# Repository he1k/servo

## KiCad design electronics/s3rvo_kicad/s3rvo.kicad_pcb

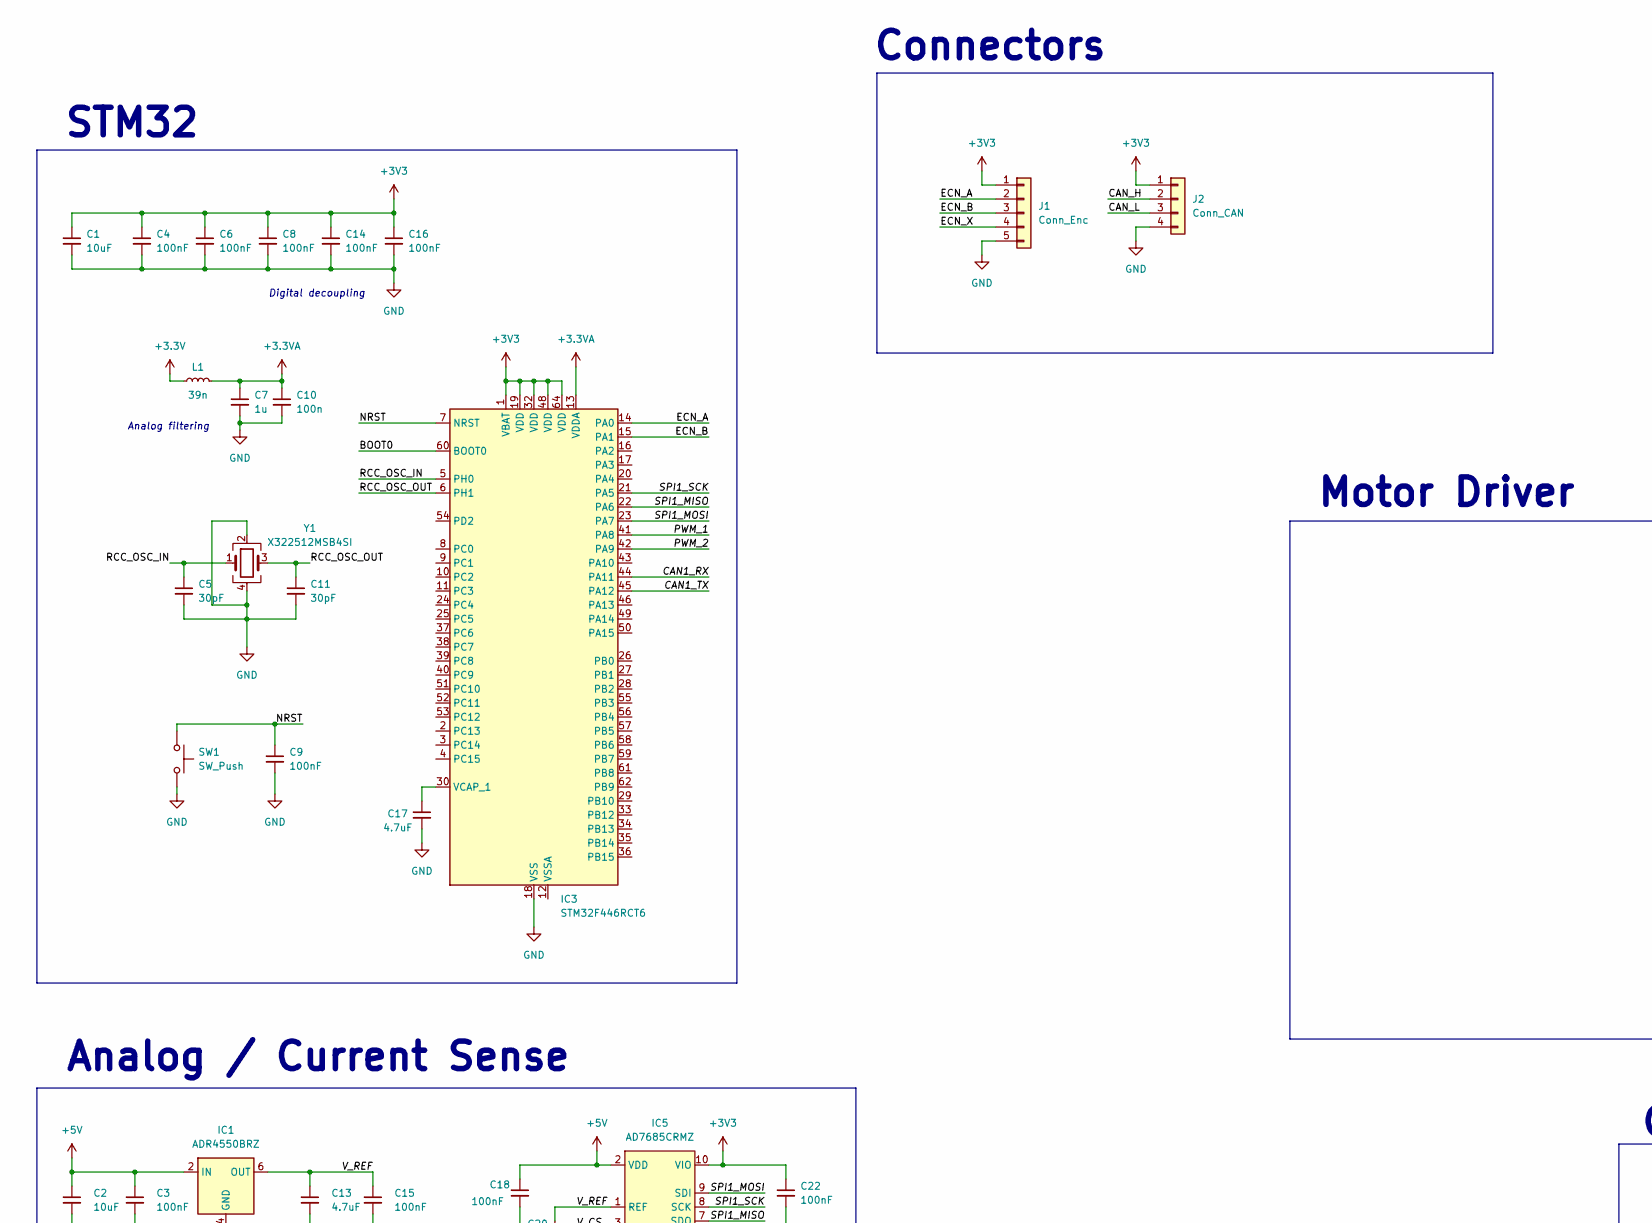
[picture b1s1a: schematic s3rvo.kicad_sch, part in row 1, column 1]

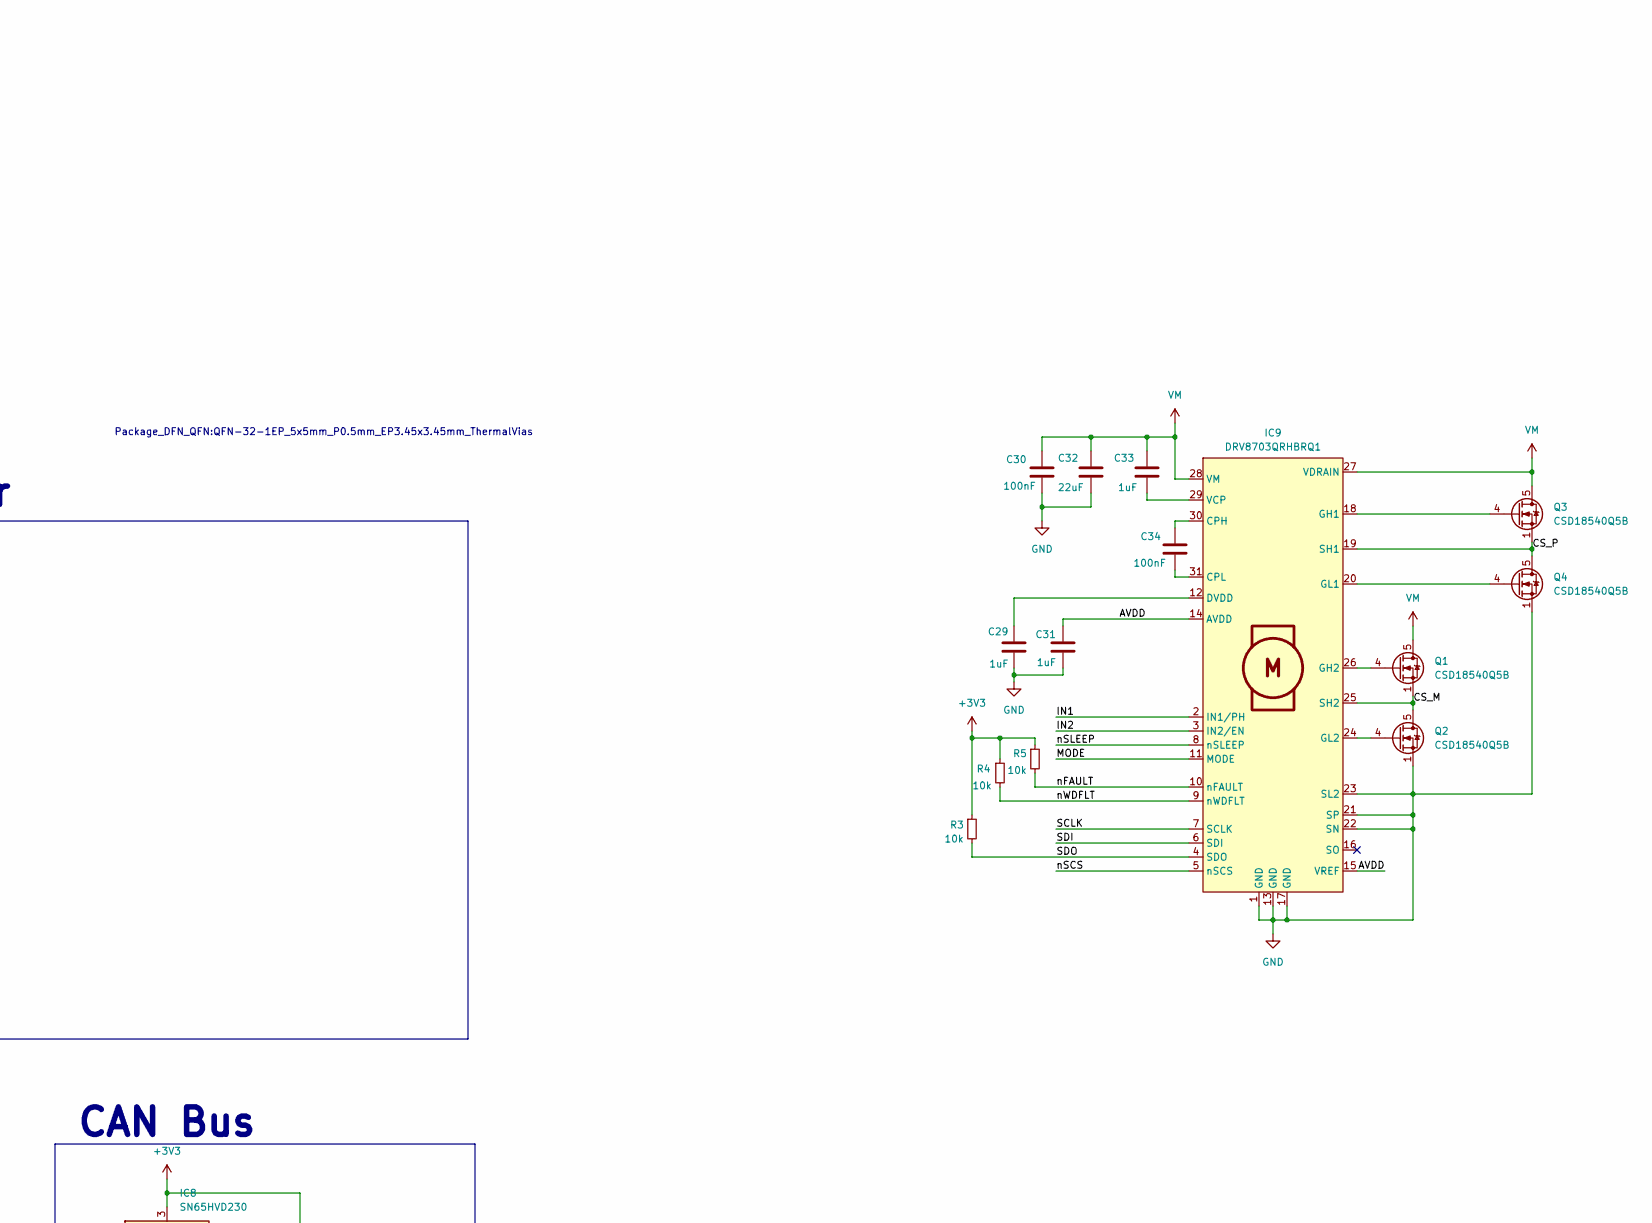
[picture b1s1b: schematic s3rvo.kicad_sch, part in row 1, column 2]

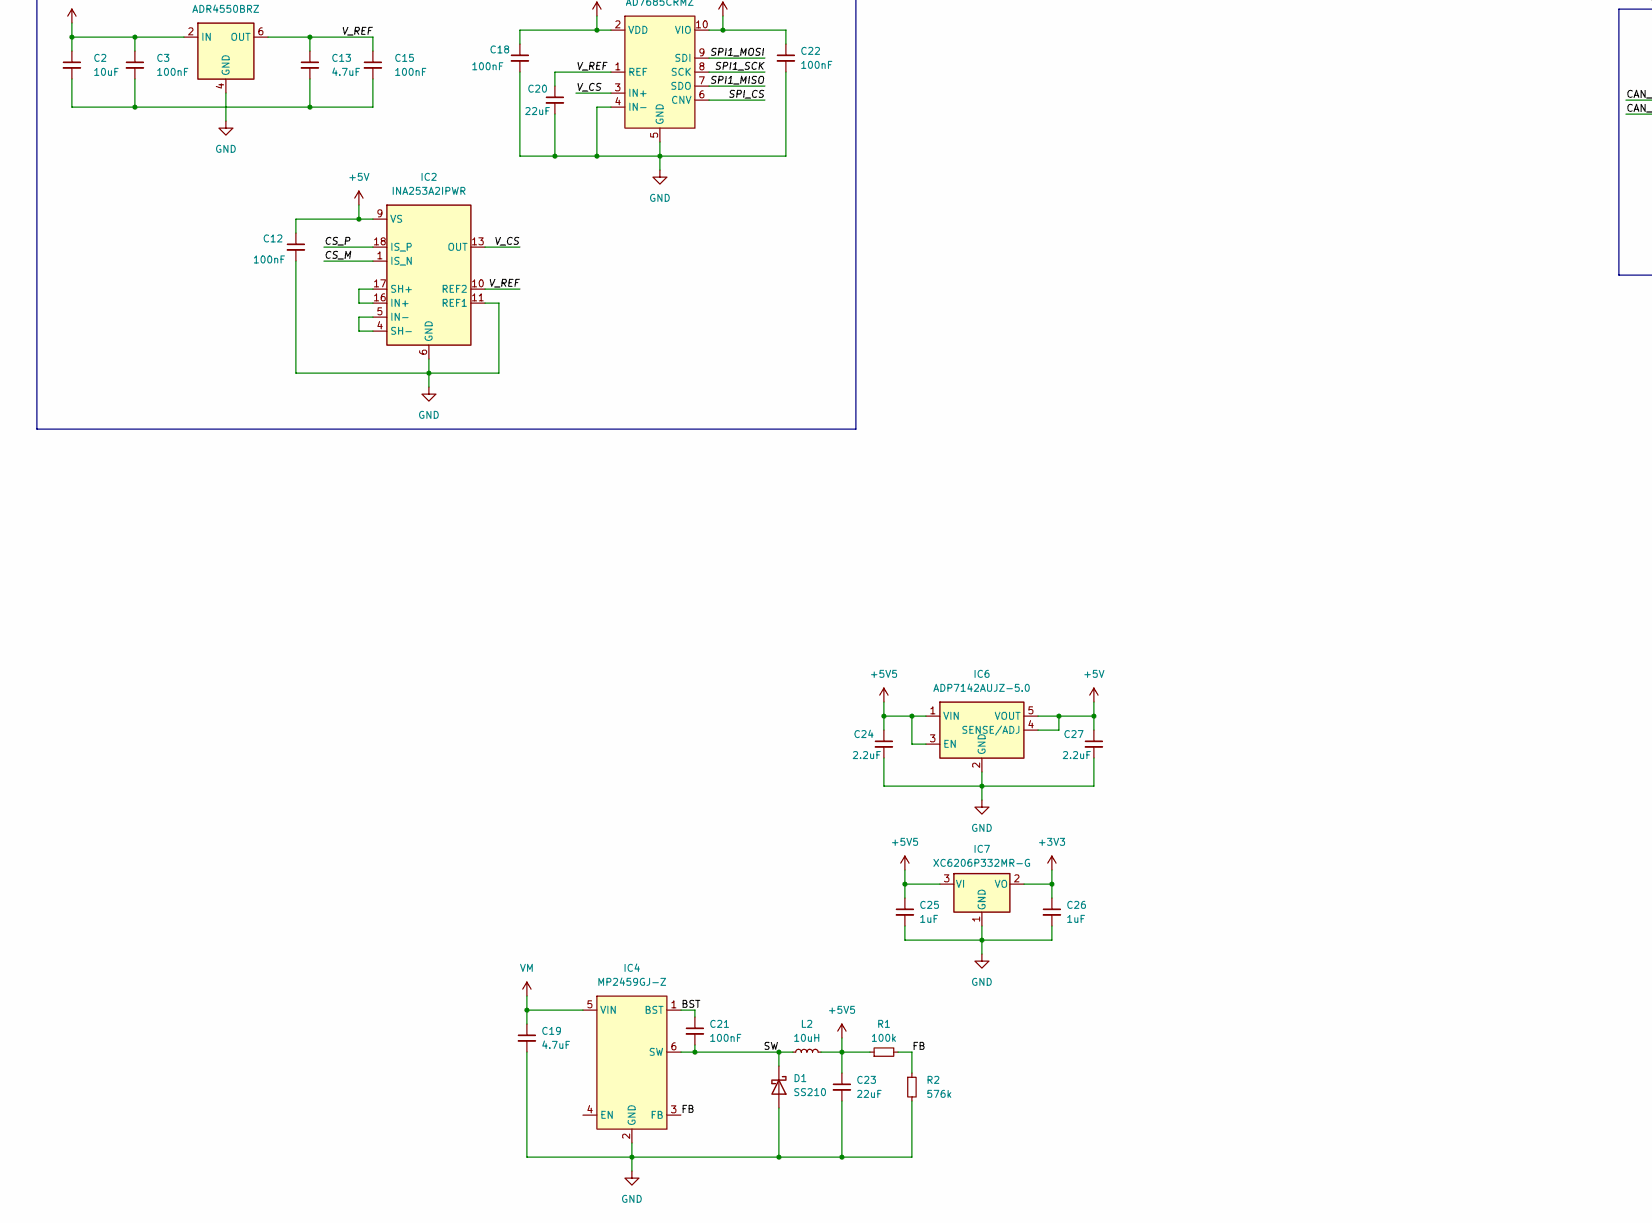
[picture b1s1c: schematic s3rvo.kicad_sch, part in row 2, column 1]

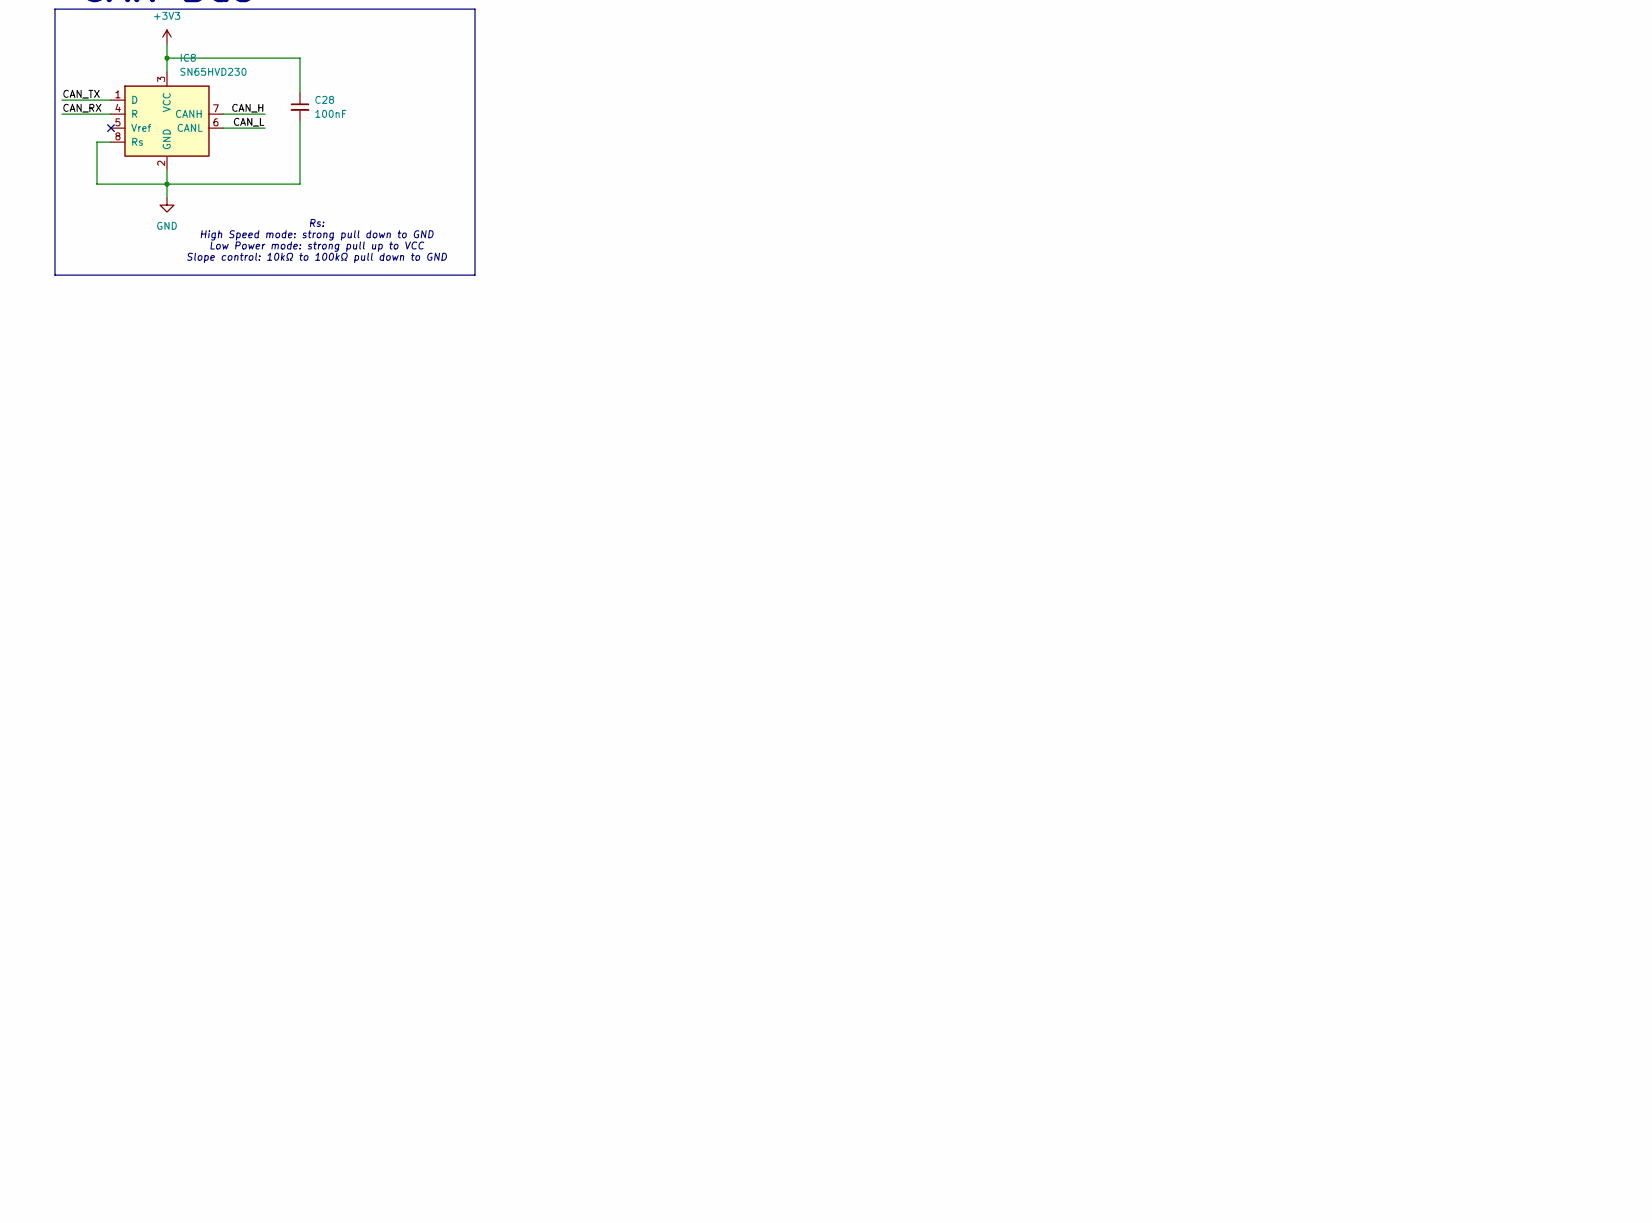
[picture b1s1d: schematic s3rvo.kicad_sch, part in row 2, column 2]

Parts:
C1: 10uF; C_0603_1608Metric; LCSC C19702
C2: 10uF; C_0603_1608Metric
C3, C12, C15, C18, C21, C22, C28: 100nF; C_0402_1005Metric
C4, C6, C8, C9, C14, C16: 100nF; C_0402_1005Metric; LCSC C1525
C5, C11: 30pF; C_0603_1608Metric; LCSC C1658
C7: 1u; C_0402_1005Metric; LCSC C52923
C10: 100n; C_0402_1005Metric; LCSC C1525
C13, C17, C19: 4.7uF; C_0603_1608Metric
C20, C23: 22uF; C_0603_1608Metric
C24, C27: 2.2uF; C_0603_1608Metric
C25, C26: 1uF; C_0603_1608Metric
C29, C31, C33: 1uF; C_0201_0603Metric
C30, C34: 100nF; C_0201_0603Metric
C32: 22uF; C_0201_0603Metric
D1: SS210; D_SMA; LCSC C14996
IC1: ADR4550BRZ; SOIC-8_3.9x4.9mm_P1.27mm
IC2: INA253A2IPWR; TSSOP-20_4.4x6.5mm_P0.65mm
IC3: STM32F446RCT6; LQFP-64_10x10mm_P0.5mm; LCSC C915971
IC4: MP2459GJ-Z; TSOT-23-6; LCSC C39578
IC5: AD7685CRMZ; MSOP-10_3x3mm_P0.5mm
IC6: ADP7142AUJZ-5.0; TSOT-23-5; LCSC C659367
IC7: XC6206P332MR-G; SOT-23-3; LCSC C5446
IC8: SN65HVD230; SOIC-8_3.9x4.9mm_P1.27mm
IC9: DRV8703QRHBRQ1; QFN-32-1EP_5x5mm_P0.5mm_EP3.45x3.45mm_ThermalVias; LCSC C181573
J1: Conn_Enc; Molex_PicoBlade_53047-0510_1x05_P1.25mm_Vertical
J2: Conn_CAN; Molex_PicoBlade_53048-0410_1x04_P1.25mm_Horizontal
L1: 39n; L_0402_1005Metric; LCSC C26443
L2: 10uH; L_Coilcraft_LPS5030; LCSC C20417074
Q1, Q2, Q3, Q4: CSD18540Q5B; TDSON-8-1
R1: 100k; R_0402_1005Metric
R2: 576k; R_0402_1005Metric
R3, R4, R5: 10k; R_0402_1005Metric
SW1: SW_Push; SW_Push_SPST_NO_Alps_SKRK; LCSC C202388
Y1: X322512MSB4SI; Crystal_SMD_3225-4Pin_3.2x2.5mm; LCSC C9002

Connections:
+3.3V: L1.1
+3.3VA: C7.1, C10.1, IC3.13 (VDDA), L1.2
+3V3: C1.1, C4.1, C6.1, C8.1, C14.1, C16.1, C22.1, C26.1, C28.1, IC3.1 (VBAT), IC3.19 (VDD), IC3.32 (VDD), IC3.48 (VDD), IC3.64 (VDD), IC5.10 (VIO), IC7.2 (VO), IC8.3 (VCC), J1.1, J2.1, R3.1, R4.1, R5.1
+5V: C2.1, C3.1, C12.1, C18.1, C27.1, IC1.2 (IN), IC2.9 (VS), IC5.2 (VDD), IC6.4 (SENSE/ADJ), IC6.5 (VOUT)
+5V5: C23.1, C24.1, C25.1, IC6.1 (VIN), IC6.3 (EN), IC7.3 (VI), L2.2, R1.1
/AVDD: C31.1, IC9.14 (AVDD), IC9.15 (VREF)
/BOOT0: IC3.60 (BOOT0)
/BST: C21.1, IC4.1 (BST)
/CAN1_RX: IC3.44 (PA11)
/CAN1_TX: IC3.45 (PA12)
/CAN_H: IC8.7 (CANH), J2.2
/CAN_L: IC8.6 (CANL), J2.3
/CAN_RX: IC8.4 (R)
/CAN_TX: IC8.1 (D)
/CS_M: IC2.1 (IS_N), IC9.25 (SH2), Q1.1 (S), Q1.2 (S), Q1.3 (S), Q2.5 (D)
/CS_P: IC2.18 (IS_P), IC9.19 (SH1), Q3.1 (S), Q3.2 (S), Q3.3 (S), Q4.5 (D)
/ECN_A: IC3.14 (PA0), J1.2
/ECN_B: IC3.15 (PA1), J1.3
/ECN_X: J1.4
/FB: IC4.3 (FB), R1.2, R2.1
/IN1: IC9.2 (IN1/PH)
/IN2: IC9.3 (IN2/EN)
/MODE: IC9.11 (MODE)
/NRST: C9.1, IC3.7 (NRST), SW1.1
/PWM_1: IC3.41 (PA8)
/PWM_2: IC3.42 (PA9)
/RCC_OSC_IN: C5.1, IC3.5 (PH0), Y1.1
/RCC_OSC_OUT: C11.1, IC3.6 (PH1), Y1.3
/SCLK: IC9.7 (SCLK)
/SDI: IC9.6 (SDI)
/SDO: IC9.4 (SDO), R3.2
/SPI1_MISO: IC3.22 (PA6), IC5.7 (SDO)
/SPI1_MOSI: IC3.23 (PA7), IC5.9 (SDI)
/SPI1_SCK: IC3.21 (PA5), IC5.8 (SCK)
/SPI_CS: IC5.6 (CNV)
/SW: C21.2, D1.1 (K), IC4.6 (SW), L2.1
/V_CS: IC2.13 (OUT), IC5.3 (IN+)
/V_REF: C13.1, C15.1, C20.1, IC1.6 (OUT), IC2.10 (REF2), IC5.1 (REF)
/nFAULT: IC9.10 (nFAULT), R5.2
/nSCS: IC9.5 (nSCS)
/nSLEEP: IC9.8 (nSLEEP)
/nWDFLT: IC9.9 (nWDFLT), R4.2
GND: C1.2, C4.2, C5.2, C6.2, C7.2, C8.2, C9.2, C10.2, C11.2, C12.2, C14.2, C16.2, C17.2, C18.2, C19.2, C20.2, C22.2, C23.2, C24.2, C25.2, C26.2, C27.2, C28.2, C29.2, C30.2, C31.2, C32.2, D1.2 (A), IC1.4 (GND), IC2.6 (GND), IC2.11 (REF1), IC2.15 (GND), IC3.18 (VSS), IC3.31 (VSS), IC3.47 (VSS), IC3.63 (VSS), IC4.2 (GND), IC5.4 (IN-), IC5.5 (GND), IC6.2 (GND), IC7.1 (GND), IC8.2 (GND), IC8.8 (Rs), IC9.1 (GND), IC9.13 (GND), IC9.17 (GND), IC9.21 (SP), IC9.22 (SN), IC9.23 (SL2), J1.5, J2.4, Q2.1 (S), Q2.2 (S), Q2.3 (S), Q4.1 (S), Q4.2 (S), Q4.3 (S), R2.2, SW1.2, Y1.2, Y1.4
unnamed: C2.2, C3.2, C13.2, C15.2
unnamed: IC2.16 (IN+), IC2.17 (SH+)
unnamed: IC2.4 (SH-), IC2.5 (IN-)
unnamed: C17.1, IC3.30 (VCAP_1)
unnamed: C34.1, IC9.30 (CPH)
unnamed: C34.2, IC9.31 (CPL)
unnamed: C29.1, IC9.12 (DVDD)
unnamed: IC9.18 (GH1), Q3.4 (G)
unnamed: IC9.26 (GH2), Q1.4 (G)
unnamed: IC9.20 (GL1), Q4.4 (G)
unnamed: IC9.24 (GL2), Q2.4 (G)
unnamed: C33.2, IC9.29 (VCP)
VM: C19.1, C30.1, C32.1, C33.1, IC4.5 (VIN), IC9.27 (VDRAIN), IC9.28 (VM), Q1.5 (D), Q3.5 (D)

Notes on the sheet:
Digital decoupling
Package_DFN_QFN:QFN-32-1EP_5x5mm_P0.5mm_EP3.45x3.45mm_ThermalVias
Analog / Current Sense
Motor Driver
Analog filtering
Rs: High Speed mode: strong pull down to GND Low Power mode: strong pull up to VCC Slope control: 10kΩ to 100kΩ pull down to GND
Connectors
CAN Bus
STM32

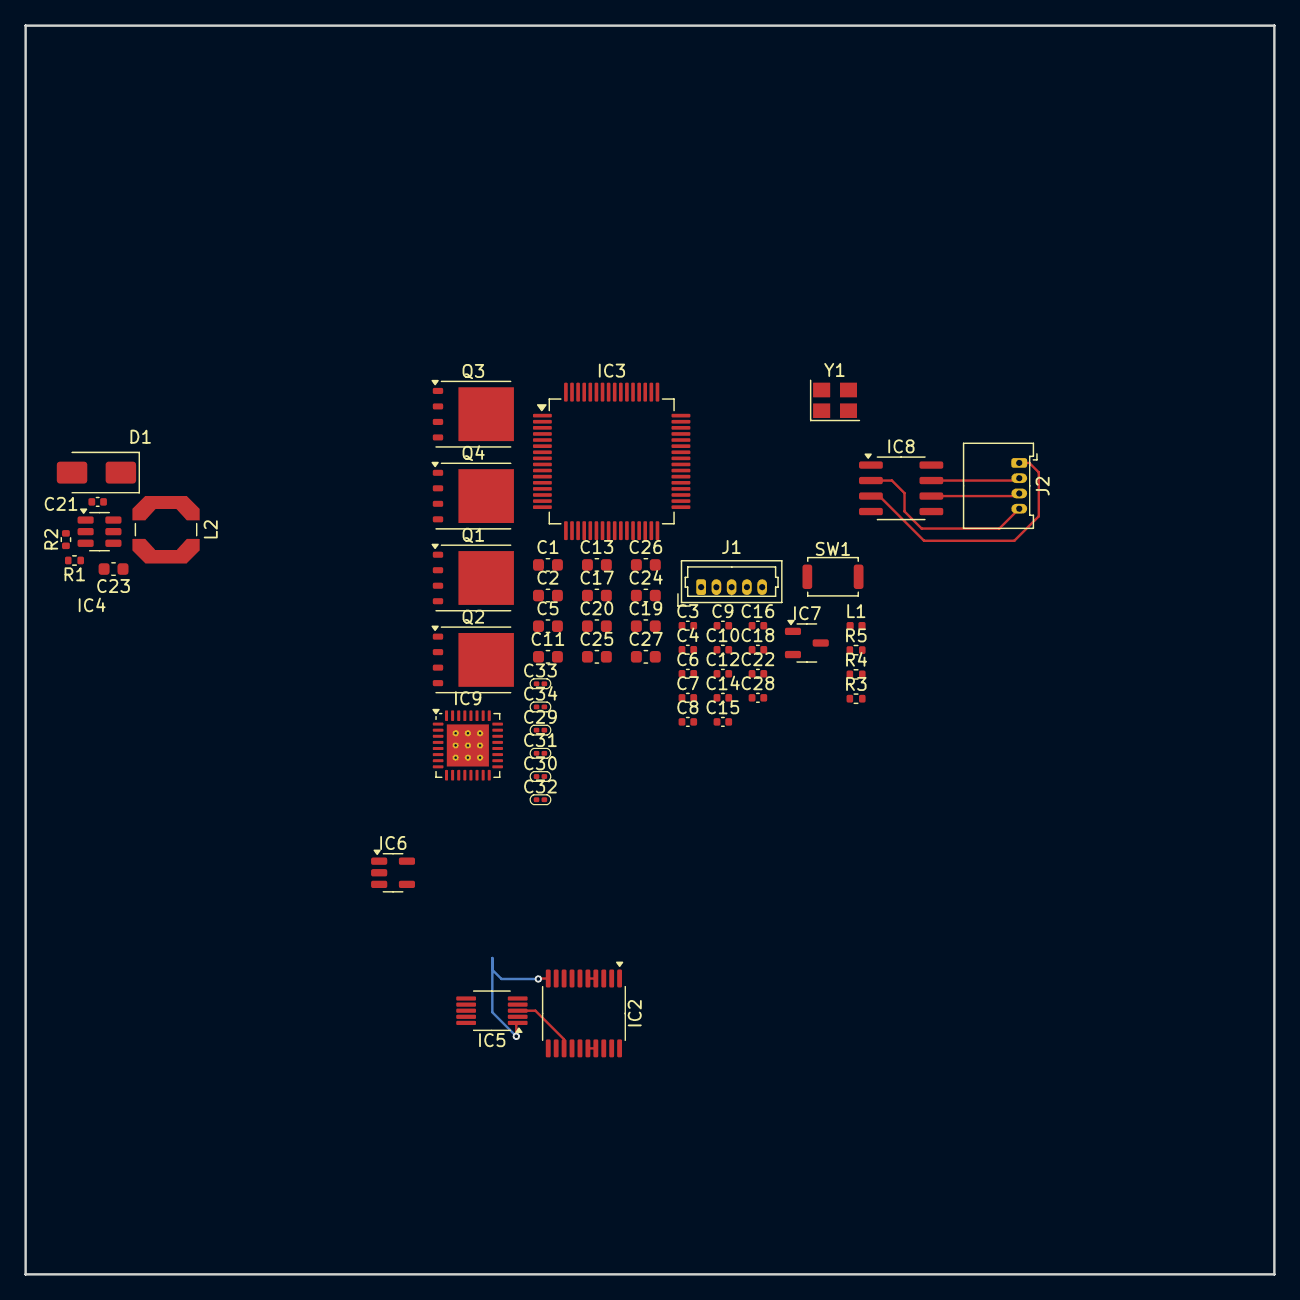
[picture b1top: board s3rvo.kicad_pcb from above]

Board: 4 copper layers, 102.3 x 102.3 mm, 59 parts (1 on the bottom side), 39 nets.

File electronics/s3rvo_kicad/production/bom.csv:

Designator,Footprint,Quantity,Value,LCSC Part #
C1,0603,1,10uF,C19702
C10,0402,1,100n,C1525
"C11, C5",0603,2,30pF,C1658
"C12, C15, C18, C21, C22, C28, C3",0402,7,100nF,
"C13, C17, C19",0603,3,4.7uF,
"C14, C16, C4, C6, C8, C9",0402,6,100nF,C1525
C2,0603,1,10uF,
"C20, C23",0603,2,22uF,
"C24, C27",0603,2,2.2uF,
"C25, C26",0603,2,1uF,
"C29, C31, C33",0201,3,1uF,
"C30, C34",0201,2,100nF,
C32,0201,1,22uF,
C7,0402,1,1u,C52923
D1,D_SMA,1,SS210,C14996
IC1,SOIC-8_3.9x4.9mm_P1.27mm,1,ADR4550BRZ,
IC2,TSSOP-20_4.4x6.5mm_P0.65mm,1,INA253A2IPWR,
IC3,LQFP-64_10x10mm_P0.5mm,1,STM32F446RCT6,C915971
IC4,TSOT-23-6,1,MP2459GJ-Z,C39578
IC5,MSOP-10_3x3mm_P0.5mm,1,AD7685CRMZ,
IC6,TSOT-23-5,1,ADP7142AUJZ-5.0,C659367
IC7,SOT-23-3,1,XC6206P332MR-G,C5446
IC8,SOIC-8_3.9x4.9mm_P1.27mm,1,SN65HVD230,
IC9,QFN-32-1EP_5x5mm_P0.5mm_EP3.45x3.45mm_ThermalVias,1,DRV8703QRHBRQ1,C181573
J1,Molex_PicoBlade_53047-0510_1x05_P1.25mm_Vertical,1,Conn_Enc,
J2,Molex_PicoBlade_53048-0410_1x04_P1.25mm_Horizontal,1,Conn_CAN,
L1,0402,1,39n,C26443
L2,L_Coilcraft_LPS5030,1,10uH,C20417074
"Q1, Q2, Q3, Q4",TDSON-8-1,4,CSD18540Q5B,
R1,0402,1,100k,
R2,0402,1,576k,
"R3, R4, R5",0402,3,10k,
SW1,SW_Push_SPST_NO_Alps_SKRK,1,SW_Push,C202388
Y1,Crystal_SMD_3225-4Pin_3.2x2.5mm,1,X322512MSB4SI, C9002

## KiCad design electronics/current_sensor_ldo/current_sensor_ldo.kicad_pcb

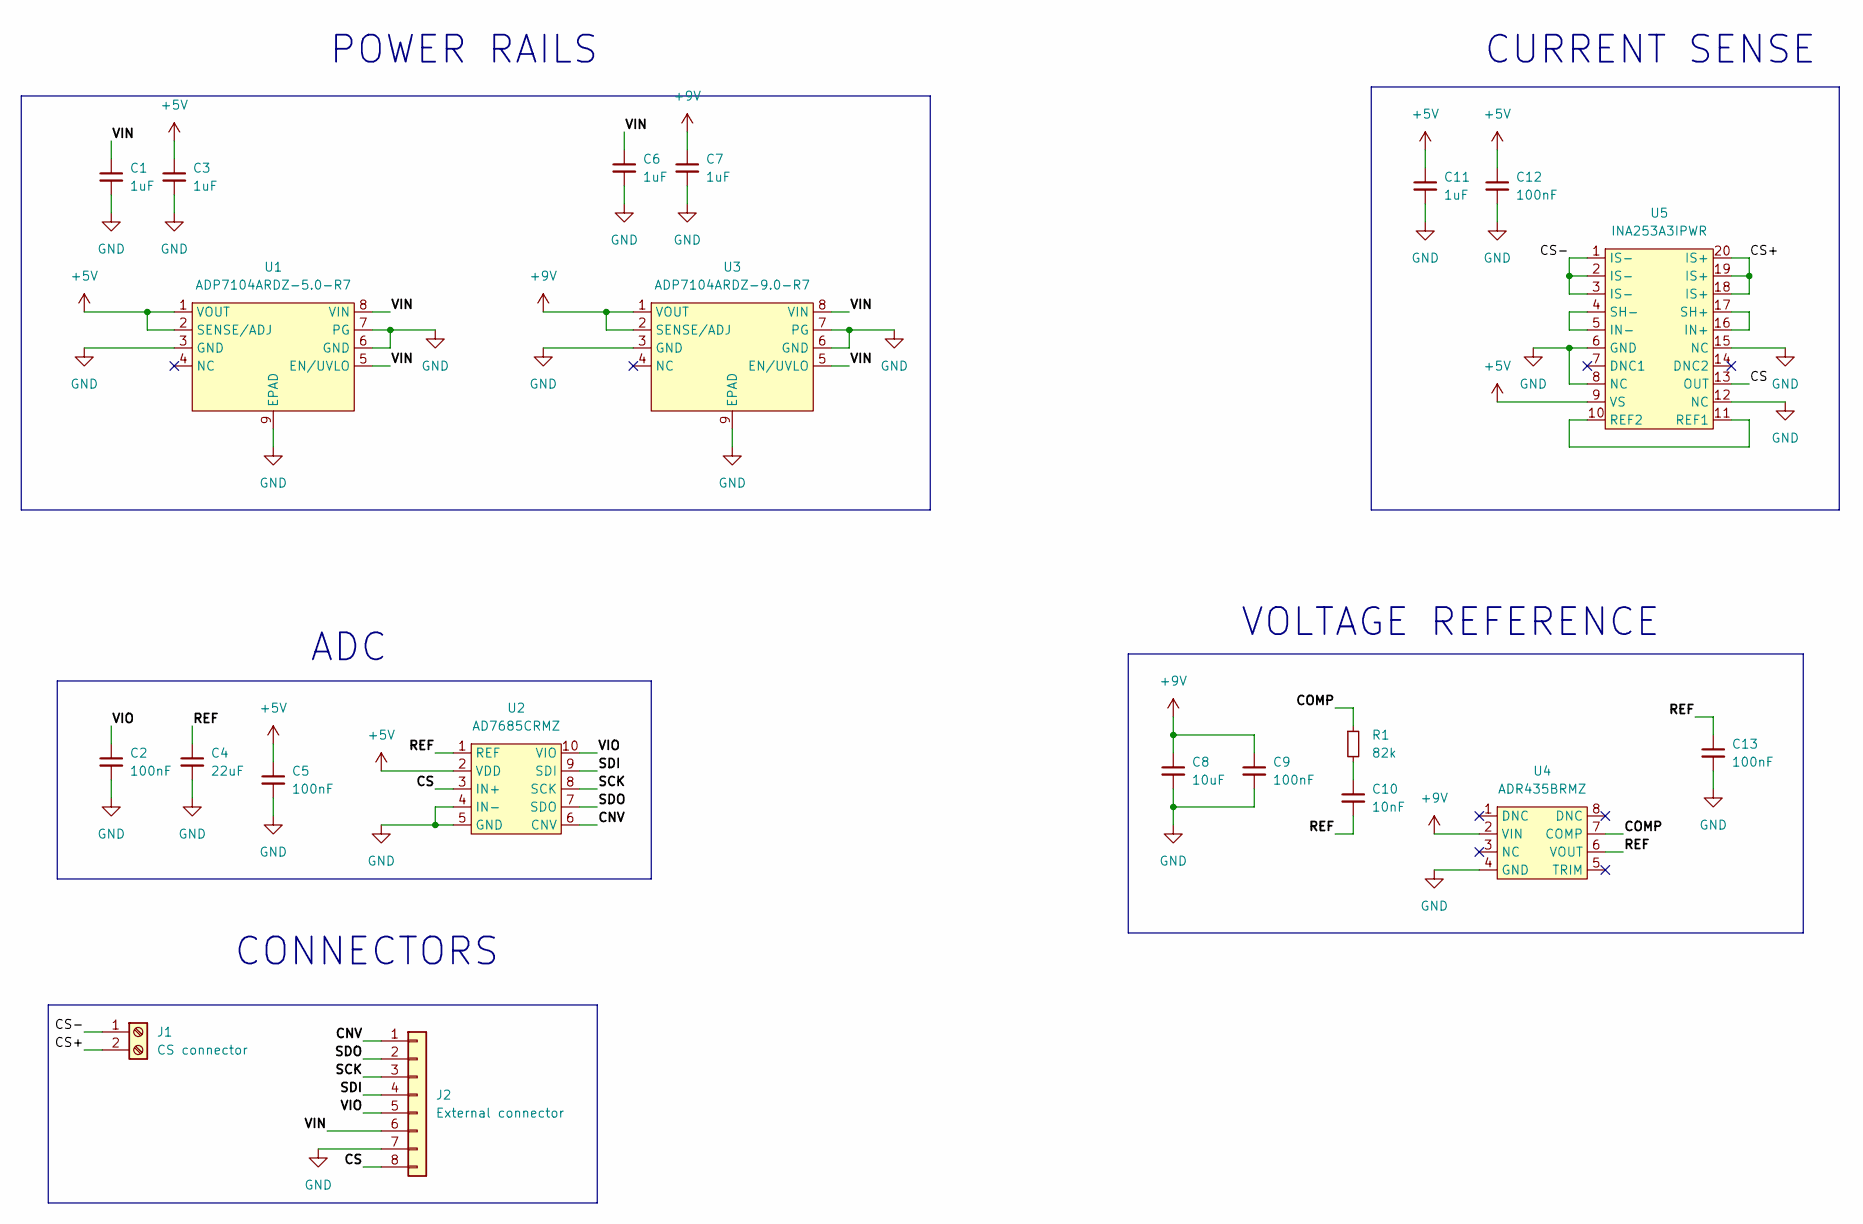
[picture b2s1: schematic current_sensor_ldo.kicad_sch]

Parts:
C1, C3, C6, C7, C11: 1uF; C_1206_3216Metric_Pad1.33x1.80mm_HandSolder
C2, C5, C9, C12, C13: 100nF; C_0805_2012Metric_Pad1.18x1.45mm_HandSolder
C4: 22uF; C_1206_3216Metric_Pad1.33x1.80mm_HandSolder
C8: 10uF; C_0805_2012Metric_Pad1.18x1.45mm_HandSolder
C10: 10nF; C_0805_2012Metric_Pad1.18x1.45mm_HandSolder
J1: CS connector; PinHeader_1x02_P2.54mm_Vertical
J2: External connector; PinHeader_1x08_P2.54mm_Vertical
R1: 82k; R_0805_2012Metric_Pad1.20x1.40mm_HandSolder
U1: ADP7104ARDZ-5.0-R7; SOIC-8-1EP_3.9x4.9mm_P1.27mm_EP2.41x3.81mm
U2: AD7685CRMZ; MSOP-10_3x3mm_P0.5mm
U3: ADP7104ARDZ-9.0-R7; SOIC-8-1EP_3.9x4.9mm_P1.27mm_EP2.41x3.81mm
U4: ADR435BRMZ; MSOP-8_3x3mm_P0.65mm
U5: INA253A3IPWR; TSSOP-20_4.4x6.5mm_P0.65mm

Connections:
+5V: C3.1, C5.1, C11.1, C12.1, U1.1 (VOUT), U1.2 (SENSE/ADJ), U2.2 (VDD), U5.9 (VS)
+9V: C7.1, C8.1, C9.1, U3.1 (VOUT), U3.2 (SENSE/ADJ), U4.2 (VIN)
/CNV: J2.1, U2.6 (CNV)
/COMP: R1.1, U4.7 (COMP)
/CS: J2.8, U2.3 (IN+), U5.13 (OUT)
/CS+: J1.2, U5.18 (IS+), U5.19 (IS+), U5.20 (IS+)
/CS-: J1.1, U5.1 (IS-), U5.2 (IS-), U5.3 (IS-)
/REF: C4.1, C10.2, C13.1, U2.1 (REF), U4.6 (VOUT)
/SCK: J2.3, U2.8 (SCK)
/SDI: J2.4, U2.9 (SDI)
/SDO: J2.2, U2.7 (SDO)
/VIN: C1.1, C6.1, J2.6, U1.5 (EN/UVLO), U1.8 (VIN), U3.5 (EN/UVLO), U3.8 (VIN)
/VIO: C2.1, J2.5, U2.10 (VIO)
GND: C1.2, C2.2, C3.2, C4.2, C5.2, C6.2, C7.2, C8.2, C9.2, C11.2, C12.2, C13.2, J2.7, U1.3 (GND), U1.6 (GND), U1.7 (PG), U1.9 (EPAD), U2.4 (IN-), U2.5 (GND), U3.3 (GND), U3.6 (GND), U3.7 (PG), U3.9 (EPAD), U4.4 (GND), U5.6 (GND), U5.8 (NC), U5.12 (NC), U5.15 (NC)
unnamed: C10.1, R1.2
unnamed: U5.16 (IN+), U5.17 (SH+)
unnamed: U5.4 (SH-), U5.5 (IN-)
unnamed: U5.10 (REF2), U5.11 (REF1)

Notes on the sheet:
CURRENT SENSE
POWER RAILS
CONNECTORS
ADC
VOLTAGE REFERENCE

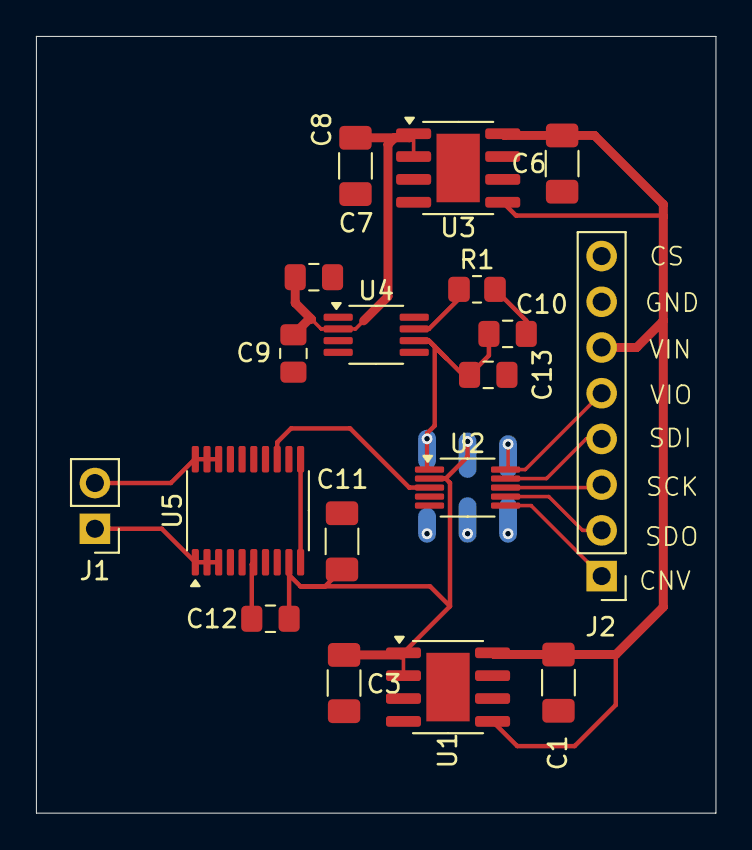
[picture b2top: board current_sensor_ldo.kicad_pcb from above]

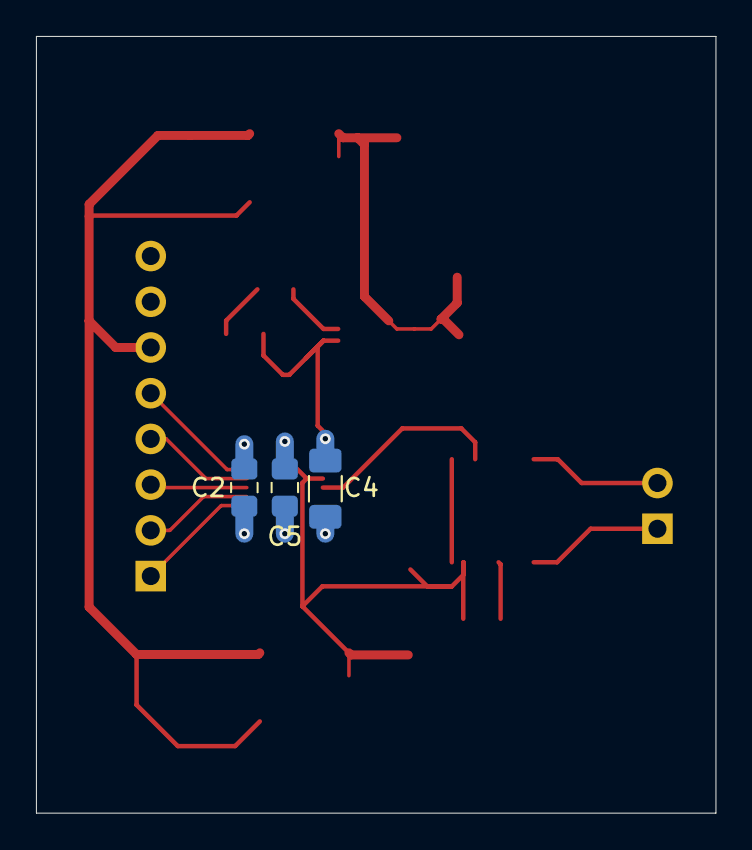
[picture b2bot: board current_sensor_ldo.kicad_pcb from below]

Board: 2 copper layers, 37.8 x 43.1 mm, 21 parts (3 on the bottom side), 18 nets.

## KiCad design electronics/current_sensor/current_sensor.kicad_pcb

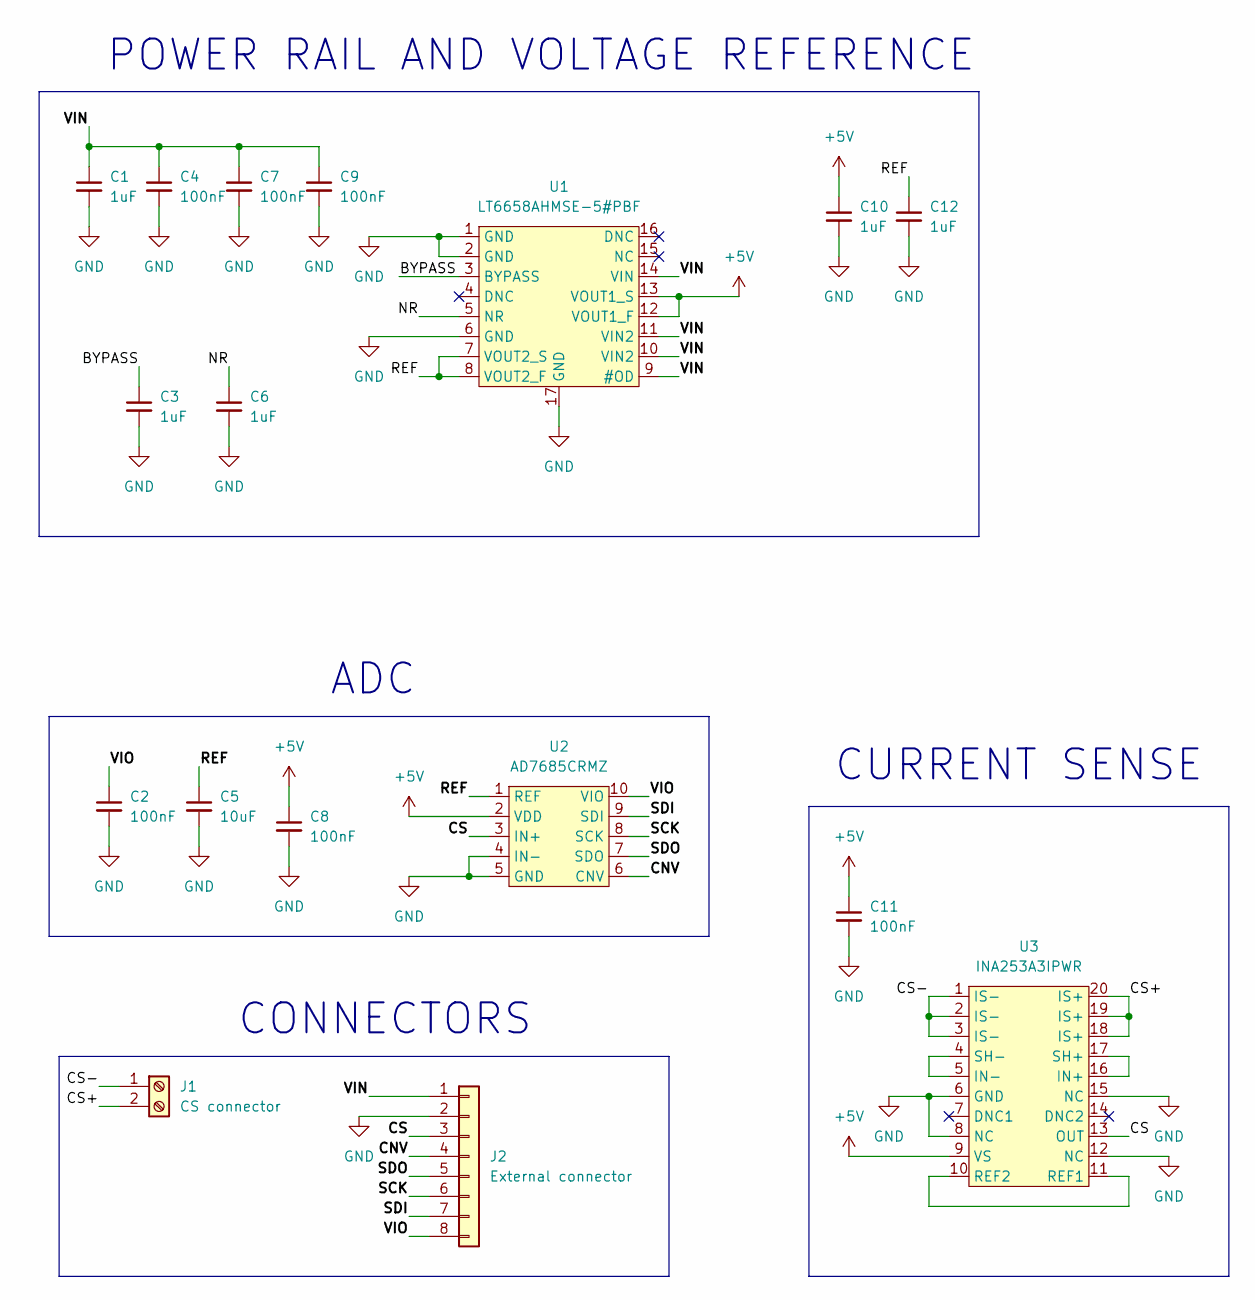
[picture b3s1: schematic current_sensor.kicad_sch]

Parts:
C1: 1uF; C_1206_3216Metric_Pad1.33x1.80mm_HandSolder
C2, C4, C7, C8, C9, C11: 100nF; C_0805_2012Metric_Pad1.18x1.45mm_HandSolder
C3, C6, C10, C12: 1uF; C_0805_2012Metric_Pad1.18x1.45mm_HandSolder
C5: 10uF; C_0805_2012Metric_Pad1.18x1.45mm_HandSolder
J1: CS connector; PinHeader_1x02_P2.54mm_Vertical
J2: External connector; PinHeader_1x08_P2.54mm_Vertical
U1: LT6658AHMSE-5#PBF; MSOP-16-1EP_3x4.039mm_P0.5mm_EP1.651x2.845mm
U2: AD7685CRMZ; MSOP-10_3x3mm_P0.5mm
U3: INA253A3IPWR; TSSOP-20_4.4x6.5mm_P0.65mm

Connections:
+5V: C8.1, C10.1, C11.1, U1.12 (VOUT1_F), U1.13 (VOUT1_S), U2.2 (VDD), U3.9 (VS)
/BYPASS: C3.1, U1.3 (BYPASS)
/CNV: J2.4, U2.6 (CNV)
/CS: J2.3, U2.3 (IN+), U3.13 (OUT)
/CS+: J1.2, U3.18 (IS+), U3.19 (IS+), U3.20 (IS+)
/CS-: J1.1, U3.1 (IS-), U3.2 (IS-), U3.3 (IS-)
/NR: C6.1, U1.5 (NR)
/REF: C5.1, C12.1, U1.7 (VOUT2_S), U1.8 (VOUT2_F), U2.1 (REF)
/SCK: J2.6, U2.8 (SCK)
/SDI: J2.7, U2.9 (SDI)
/SDO: J2.5, U2.7 (SDO)
/VIN: C1.1, C4.1, C7.1, C9.1, J2.1, U1.9 (#OD), U1.10 (VIN2), U1.11 (VIN2), U1.14 (VIN)
/VIO: C2.1, J2.8, U2.10 (VIO)
GND: C1.2, C2.2, C3.2, C4.2, C5.2, C6.2, C7.2, C8.2, C9.2, C10.2, C11.2, C12.2, J2.2, U1.1 (GND), U1.2 (GND), U1.6 (GND), U1.17 (GND), U2.4 (IN-), U2.5 (GND), U3.6 (GND), U3.8 (NC), U3.12 (NC), U3.15 (NC)
unnamed: U3.16 (IN+), U3.17 (SH+)
unnamed: U3.4 (SH-), U3.5 (IN-)
unnamed: U3.10 (REF2), U3.11 (REF1)

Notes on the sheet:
CURRENT SENSE
POWER RAIL AND VOLTAGE REFERENCE
CONNECTORS
ADC

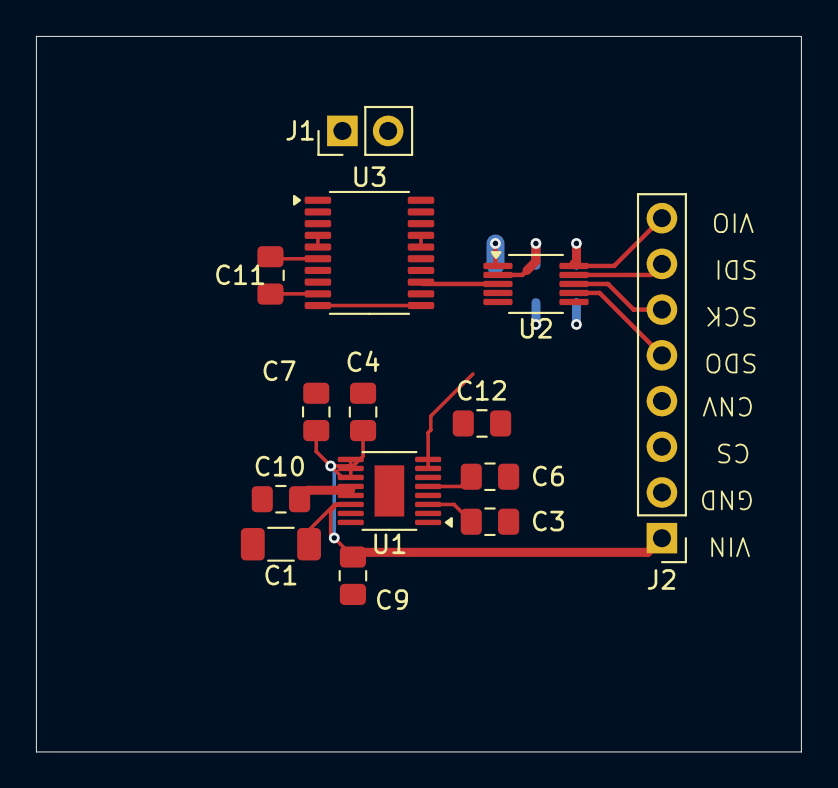
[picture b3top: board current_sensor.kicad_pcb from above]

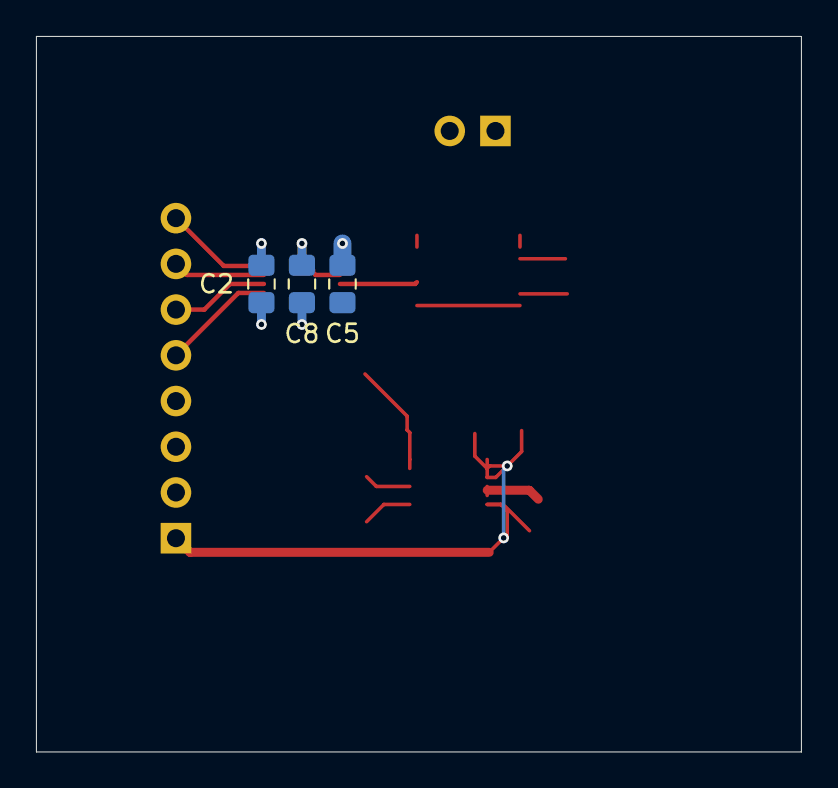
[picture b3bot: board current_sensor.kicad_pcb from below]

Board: 2 copper layers, 42.5 x 39.8 mm, 17 parts (3 on the bottom side), 17 nets.

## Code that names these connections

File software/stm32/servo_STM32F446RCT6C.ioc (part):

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Mcu.Name=STM32F446R(C-E)Tx
Mcu.Package=LQFP64
Mcu.UserName=STM32F446RCTx
PA0-WKUP.Signal=S_TIM2_CH1_ETR
PA1.Signal=S_TIM2_CH2
PA11.Mode=CAN_Activate
PA11.Signal=CAN1_RX
PA12.Mode=CAN_Activate
PA12.Signal=CAN1_TX
PA5.Mode=Full_Duplex_Master
PA5.Signal=SPI1_SCK
PA6.Mode=Full_Duplex_Master
PA6.Signal=SPI1_MISO
PA7.Mode=Full_Duplex_Master
PA7.Signal=SPI1_MOSI
PA8.Signal=S_TIM1_CH1
PA9.Signal=S_TIM1_CH2
PB0.Mode=Full_Duplex_Master
PB0.Signal=SPI3_MOSI
PB10.Mode=Full_Duplex_Master
PB10.Signal=SPI2_SCK
PC1.Mode=Full_Duplex_Master
PC1.Signal=SPI2_MOSI
PC10.Mode=Full_Duplex_Master
PC10.Signal=SPI3_SCK
PC11.Mode=Full_Duplex_Master
PC11.Signal=SPI3_MISO
PC2.Mode=Full_Duplex_Master
PC2.Signal=SPI2_MISO
PH0-OSC_IN.Mode=HSE-External-Oscillator
PH0-OSC_IN.Signal=RCC_OSC_IN
PH1-OSC_OUT.Mode=HSE-External-Oscillator
PH1-OSC_OUT.Signal=RCC_OSC_OUT
RCC.HSE_VALUE=12000000
RCC.SYSCLKFreq_VALUE=180000000
RCC.SYSCLKSource=RCC_SYSCLKSOURCE_PLLCLK
board=custom

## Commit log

2025-01-22 Update - Need to improve Storage class, very messy
2025-11-02 add tacho amplifier sim
